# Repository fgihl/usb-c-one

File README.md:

# HIL USB-C Control

A bench device that sits between a Raspberry Pi and a USB-C device under test (DUT). Host software gets controlled access to the DUT's USB 2.0 data, USB-C CC attachment and 5 V VBUS, so it can emulate unplugging and reconnecting the DUT without touching its cable.

It is intended for controlled hardware-in-the-loop (HIL) lab rigs. It is not a general-purpose USB-C charger, dock or power-distribution product.

## Features

- USB 2.0 high-speed hub with a fixed on-board control interface. The Pi always sees the controller, whether or not a DUT is connected.
- Software-controlled J3 (DUT) state: data, CC/Rp and 5 V VBUS are switched independently.
- Priority power mux: external 5 V on J2 is preferred; J1 (the Pi) is the fallback and is reverse-blocked when J2 is valid.
- J3 VBUS is protected by an eFuse (about 3.6 A typical, below 4.0 A worst case) with over-voltage protection, fault reporting and active discharge.
- Fixed 3 A Rp advertisement on J3. No USB PD, BC1.2, VCONN, SuperSpeed or alternate modes.
- One opto-buffered external control line (J4) and test points for the key rails and signals.
- Controlled via `libgpiod` on the standard Linux `cp210x` gpiochip.

## Connectors

| Ref | Role |
|---|---|
| J1 | USB-C upstream to the Raspberry Pi: USB 2.0 data, and fallback VBUS |
| J2 | USB-C 5 V power input (power only, no data). Preferred over J1 |
| J3 | USB-C downstream to the DUT: switched data, CC and VBUS |
| J4 | External opto-buffered control line |

## Architecture

```mermaid
flowchart LR
  J1[J1 USB-C to Pi] -->|D+/D-| H[CH334F USB 2.0 hub]
  J1 -->|VBUS_UP| MUX[TPS2121 priority mux]
  J2[J2 5 V input] -->|VBUS_PWR| MUX
  MUX --> VSYS((VSYS))
  VSYS --> LDO[TLV76733 3.3 V LDO]
  LDO --> H
  H -->|port 1, fixed| C[CP2102N GPIO control]
  H -->|port 2| SW[TS3USB221A data switch]
  SW --> J3[J3 USB-C to DUT]
  LDO --> RP[Rp buffer] --> J3
  VSYS --> EF[TPS259470L eFuse] -->|VBUS_HIL| J3
  C --> EF
  C --> SW
  C --> RP
```

| Function | Part |
|---|---|
| USB 2.0 hub | CH334F |
| Control IC | CP2102N-A02 (7 GPIO) |
| Power mux | TPS2121 |
| J3 eFuse | TPS259470L |
| Data switch | TS3USB221A |
| 3.3 V LDO | TLV76733 |
| Rp buffer | SN74LVC1G125 |
| ESD | TPD4E05U06 |

Board: 4 layers, 50 x 40 mm, top-side SMT, designed for JLCPCB assembly.

## Operating cases

| Case | Power source | Use |
|---|---|---|
| A. Pi-powered | J1 only | Low-current DUTs only. Enumeration, data path and low-power control. |
| B. External 5 V | J2, with the Pi supplying data on J1 | Normal mode for high-current tests. The source must supply the DUT load plus about 0.1 A board consumption (at least 3.5 A for a 3 A DUT). |
| C. Split-cable | External 5 V on J1 VBUS, Pi supplies data and GND | Qualified fixtures only. The Pi-side VBUS must be isolated from the external supply. |

J1 and J2 accept regulated 5 V only. Sustained 12 V or 20 V input is outside the product contract.

## Software contract

Software owns the state machine. The hardware does not detect DUT attach and does not enforce source capability.

- **Disconnect:** data off, wait 20 ms, CC off, wait 20 ms, VBUS off, then wait for the discharge confirmation.
- **Connect:** CC on, VBUS on, confirm VBUS present and no fault, wait 40 ms, data on.

Before a high-current test, confirm that J2 is powering the board. Turn J3 VBUS off before planned J2 removal. The CP2102N GPIO map, configuration image and a control-service example are in [architecture/architecture_final.md](architecture/architecture_final.md) section 6.

## Repository layout

| Path | Contents |
|---|---|
| [product_description.md](product_description.md) | Product requirements, operating cases, accepted limitations, acceptance checks |
| [architecture/architecture_final.md](architecture/architecture_final.md) | Schematic-level architecture, power budget, GPIO map, BOM, risks, prototype tests |
| [architecture/schematic_overview.md](architecture/schematic_overview.md) | Schematic overview |
| [architecture/pcb_floor_plan.md](architecture/pcb_floor_plan.md) | PCB floor plan and layout constraints |
| [llm-kicad/](llm-kicad/) | KiCad 10 project (hierarchical schematic, PCB, custom symbols) |
| [llm-kicad/schematic_review_report.md](llm-kicad/schematic_review_report.md) | Schematic review report and finding log |
| [tools/](tools/) | Audit and helper scripts |

The schematic sheets are `01_power_cc`, `02_usb_hub_control`, `03_dut_interface` and `04_test_validation`. Open `llm-kicad/llm-kicad.kicad_pro` in KiCad 10.

## Tools

`tools/audit_schematic.py` checks symbol pin numbers against placed footprint pad numbers, schematic versus PCB footprint sync, `Value` text versus the JLCPCB catalogue part, and `Datasheet` coverage. It exits non-zero if the pin/pad or footprint-sync checks fail.

```sh
python3 tools/audit_schematic.py
```

### Control scripts

Two self-contained host tools drive the same signal map; neither imports the other.

| Script | Host | Path to the pins |
|---|---|---|
| [code/usb-ctr-mac.py](code/usb-ctr-mac.py) | macOS | CP2102N vendor requests over libusb (pyusb) |
| [code/usb-ctr-linux.py](code/usb-ctr-linux.py) | Linux | kernel `cp210x` gpiochip (uAPI v2); usbfs for NVM reads |

Both auto-detect the board generation from the CP2102N part number and, on a QFN24, the NVM Release Version:

| Board | Part | Lines | Release Version |
|---|---|---|---|
| V2.0 | CP2102N QFN28 | 7 | `0x0200` (2.00) |
| usb-passthrough v1.1 | CP2102N QFN24 | 4 | `0x0101` (1.01, CC_EN inverted) |
| usb-passthrough v1.0 | CP2102N QFN24 | 4 | `0x0100` (1.00) |

`--board auto|v2.0|v1.1|v1.0` overrides the detection. `info` reports the identity and the programmed image, `check` is the NVM read-back gate and `verify` the full per-unit acceptance check; both accept `--record code/fleet-record.tsv`. The legacy boards have no VBUS sense, source select or opto line, so `on`/`off` substitute a settle delay for the VBUS confirmation, `ext` is refused and `--high-current` cannot be checked.

## Known limitations

- Fixed 3 A Rp: the advertisement can exceed the active source's real capacity.
- No hardware DUT-attach detection: an unplugged DUT can leave J3 VBUS live until software disables it.
- A single priority mux is the only isolation between J1 and J2. It is not an independent-source isolator, and a split cable that joins an external supply to the Pi is not protected against.
- No per-input current limit or input over-voltage disconnect.

The full list and the release acceptance checks are in [product_description.md](product_description.md) sections 7 to 9.

## Status

Hardware revision V2.0. **Five units are built, identified 1-5**, each programmed
with the CP2102N configuration image carrying **Release Version 2.00**
(`0x0200`) — the host reads this back as `bcdDevice` = `0x0200`, though only
after the board has been power-cycled. **All five units were verified
2026-10-14**: correct configuration image and power-up safe state, VBUS rising in
18–21 ms, and a USB mass-storage DUT enumerating at J3 on connect and dropping
off on disconnect. Per-unit evidence is in `code/fleet-record.tsv`. The unit ID is carried in the CP2102N USB
serial descriptor (`0001`-`0005`); the manufacturer and product strings stay at
the Silicon Labs defaults, so the serial descriptor is what distinguishes one
unit from another. See
[architecture/architecture_final.md](architecture/architecture_final.md)
section 6.3 for the Release Version and serial-number policies and the per-unit
read-back gate.

The legacy **usb-passthrough v1.1** units now carry a programmed CP2102N image
too: Release Version **1.01** (`0x0101`, which names the inverted-CC v1.1 pin
map) plus a fleet serial in the serial descriptor (`0006`, `0010`, …). Their
GPIO bytes stay at the factory open-drain/latched-high settings, so the existing
board wiring is unchanged. `check` reports PASS for such a unit and records the
read-back in `code/fleet-record.tsv` with `board = v1.1`; the host only sees the
new serial and `bcdDevice` after a power-on reset, so replug the board after
programming.

Before release, see the open items in the schematic review report and the mandatory prototype tests in [architecture/architecture_final.md](architecture/architecture_final.md) section 10. The CP2102N must be programmed with the configuration image before use.

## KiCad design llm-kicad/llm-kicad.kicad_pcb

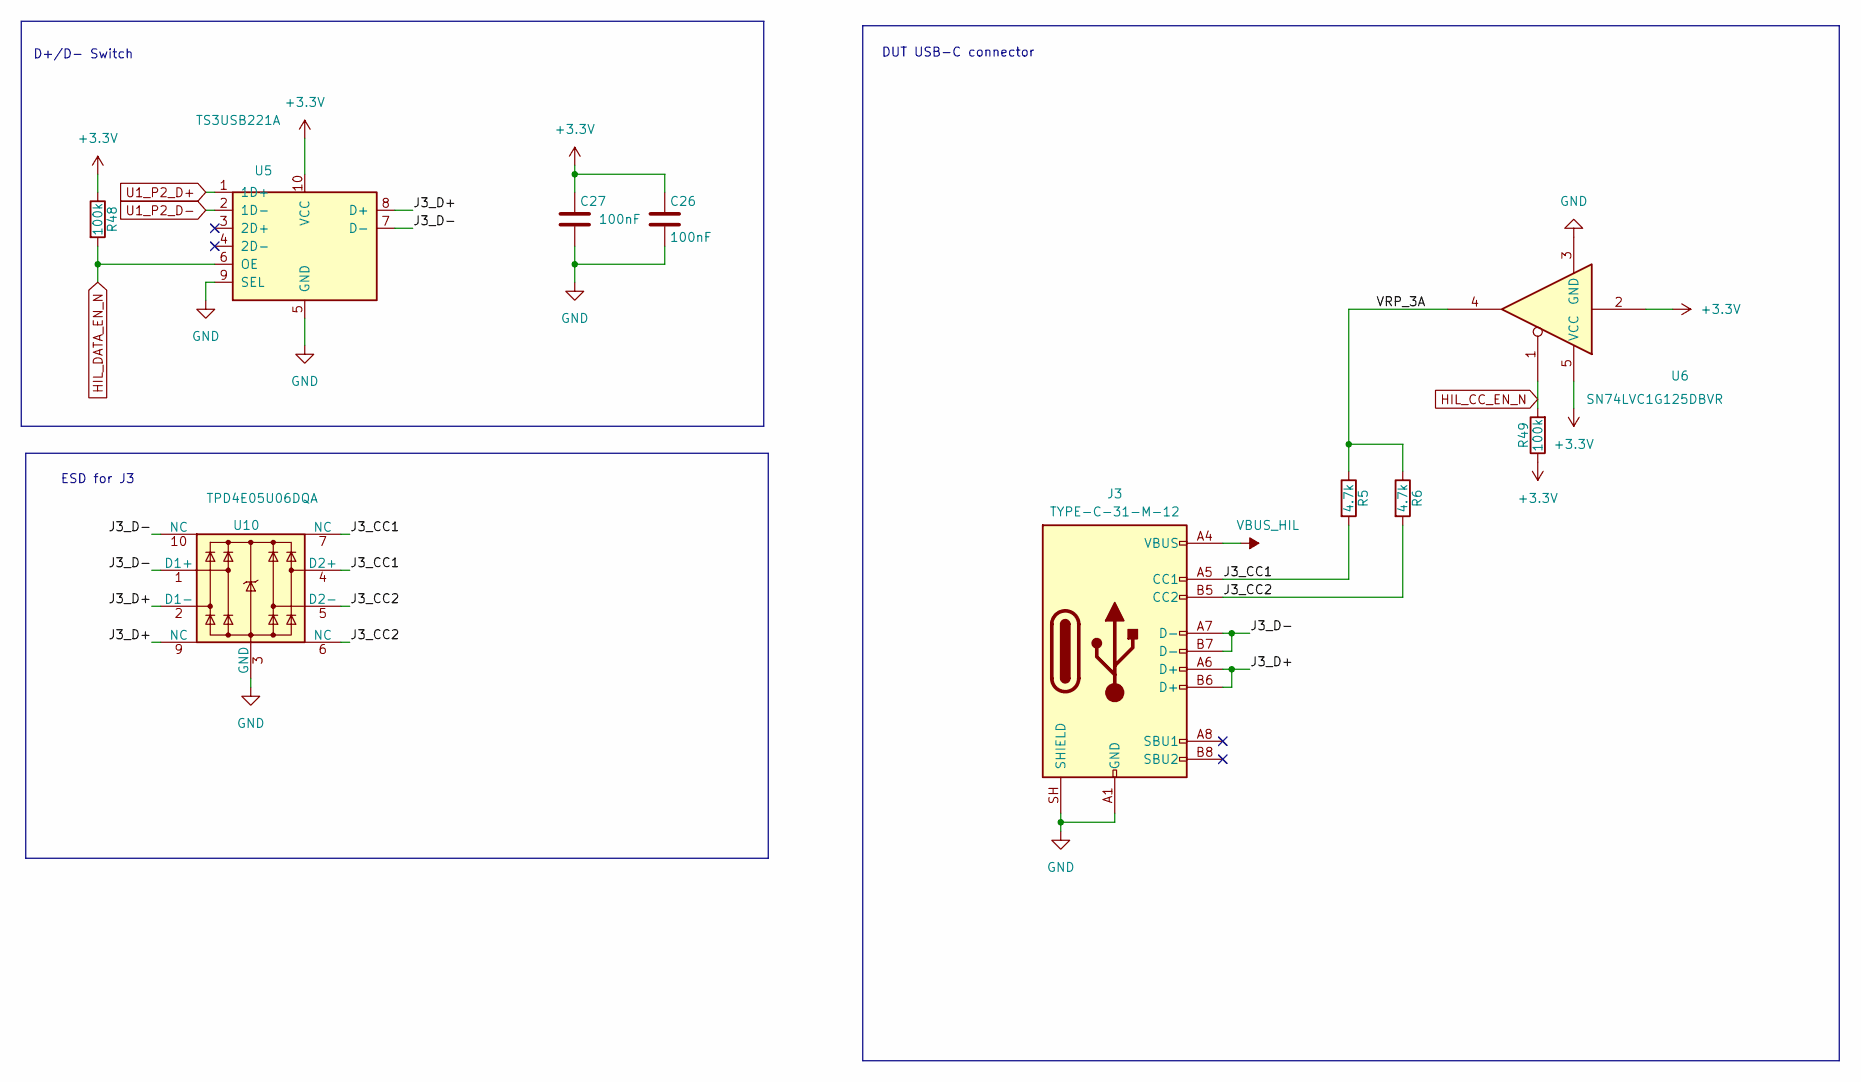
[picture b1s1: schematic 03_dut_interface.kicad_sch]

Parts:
C26, C27: 100nF; C_0402_1005Metric; LCSC C1525
J3: TYPE-C-31-M-12; USB_C_Receptacle_HRO_TYPE-C-31-M-12; LCSC C165948
R5, R6: 4.7k; R_0402_1005Metric; LCSC C25900
R48, R49: 100k; R_0402_1005Metric; LCSC C25741
U5: TS3USB221A; Texas_UQFN-10_1.5x2mm_P0.5mm; LCSC C128396
U6: SN74LVC1G125DBVR; SOT-23-5; LCSC C23654
U10: TPD4E05U06DQA; USON-10_2.5x1.0mm_P0.5mm; LCSC C138714

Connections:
+3.3V: C26.1, C27.1, R48.1, R49.1, U5.10 (VCC), U6.2, U6.5 (VCC); also elsewhere on the board
/DUT Interface/J3_CC1: J3.A5 (CC1), R5.2, U10.4 (D2+), U10.7 (NC)
/DUT Interface/J3_CC2: J3.B5 (CC2), R6.2, U10.5 (D2-), U10.6 (NC)
/DUT Interface/J3_D+: J3.A6 (D+), J3.B6 (D+), U5.8 (D+), U10.2 (D1-), U10.9 (NC)
/DUT Interface/J3_D-: J3.A7 (D-), J3.B7 (D-), U5.7 (D-), U10.1 (D1+), U10.10 (NC)
/DUT Interface/VRP_3A: R5.1, R6.1, U6.4
GND: C26.2, C27.2, J3.A1 (GND), J3.A12 (GND), J3.B1 (GND), J3.B12 (GND), J3.SH (SHIELD), U5.5 (GND), U5.9 (SEL), U6.3 (GND), U10.3 (GND), U10.8 (GND); also elsewhere on the board
HIL_CC_EN_N: R49.2, U6.1; also elsewhere on the board
HIL_DATA_EN_N: R48.2, U5.6 (OE); also elsewhere on the board
U1_P2_D+: U5.1 (1D+); also elsewhere on the board
U1_P2_D-: U5.2 (1D-); also elsewhere on the board
VBUS_HIL: J3.A4 (VBUS), J3.A9 (VBUS), J3.B4 (VBUS), J3.B9 (VBUS); also elsewhere on the board

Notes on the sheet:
DUT USB-C connector
ESD for J3
D+/D- Switch

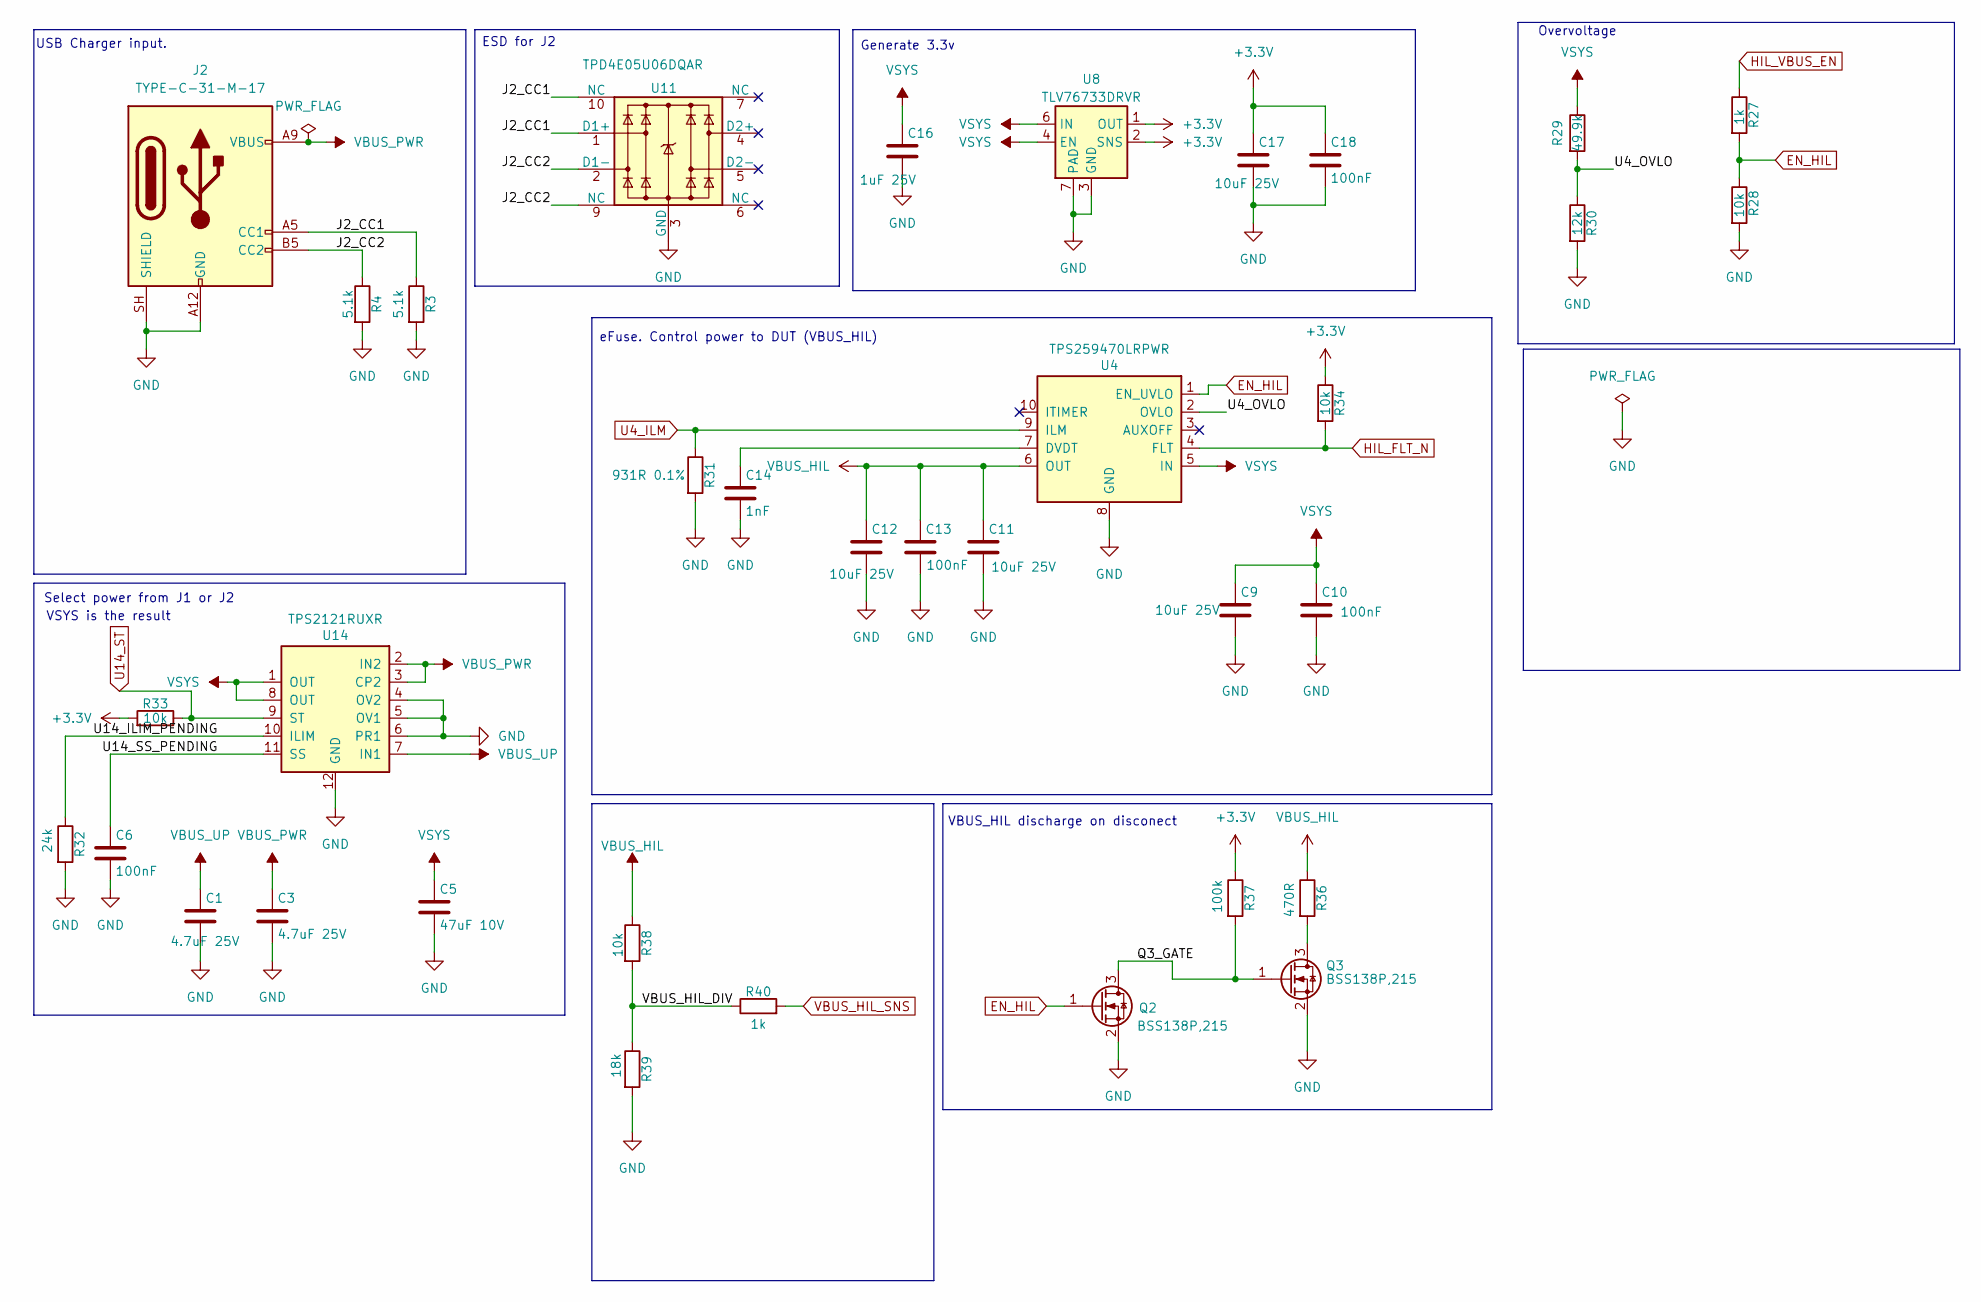
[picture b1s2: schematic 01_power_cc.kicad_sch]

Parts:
C1, C3: 4.7uF 25V; C_0805_2012Metric; LCSC C1779
C5: 47uF 10V; C_1206_3216Metric; LCSC C96123
C6, C10, C13, C18: 100nF; C_0402_1005Metric; LCSC C1525
C9, C11, C12, C17: 10uF 25V; C_0805_2012Metric; LCSC C15850
C14: 1nF; C_0402_1005Metric; LCSC C1523
C16: 1uF 25V; C_0402_1005Metric; LCSC C52923
J2: TYPE-C-31-M-17; USB_C_Receptacle_HRO_TYPE-C-31-M-17; LCSC C283540
Q2, Q3: BSS138P,215; SOT-23; LCSC C75547
R3, R4: 5.1k; R_0402_1005Metric; LCSC C25905
R27, R40: 1k; R_0402_1005Metric; LCSC C11702
R28, R33, R34, R38: 10k; R_0402_1005Metric; LCSC C25744
R29: 49.9k; R_0402_1005Metric; LCSC C25897
R30: 12k; R_0402_1005Metric; LCSC C25752
R31: 931R 0.1%; R_0402_1005Metric; LCSC C852955
R32: 24k; R_0402_1005Metric; LCSC C25769
R36: 470R; R_0805_2012Metric; LCSC C17710
R37: 100k; R_0402_1005Metric; LCSC C25741
R39: 18k; R_0402_1005Metric; LCSC C25762
U4: TPS259470LRPWR; LCSC C3662793
U8: TLV76733DRVR; WSON-6-1EP_2x2mm_P0.65mm_EP1x1.6mm_ThermalVias; LCSC C2848334
U11: TPD4E05U06DQAR; USON-10_2.5x1.0mm_P0.5mm; LCSC C138714
U14: TPS2121RUXR; Texas_VQFN-HR-12_2x2.5mm_P0.5mm; LCSC C485916

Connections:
+3.3V: C17.1, C18.1, R33.2, R34.1, R37.1, U8.1 (OUT), U8.2 (SNS); also elsewhere on the board
/Power and CC/J2_CC1: J2.A5 (CC1), R3.1, U11.1 (D1+), U11.10 (NC)
/Power and CC/J2_CC2: J2.B5 (CC2), R4.1, U11.2 (D1-), U11.9 (NC)
/Power and CC/Q3_GATE: Q2.3 (D), Q3.1 (G), R37.2
/Power and CC/U4_OVLO: R29.2, R30.1, U4.2 (OVLO)
/Power and CC/U14_ILIM_PENDING: R32.1, U14.10 (ILIM)
/Power and CC/U14_SS_PENDING: C6.1, U14.11 (SS)
/Power and CC/VBUS_HIL_DIV: R38.2, R39.1, R40.1
EN_HIL: Q2.1 (G), R27.2, R28.1, U4.1 (EN_UVLO); also elsewhere on the board
GND: C1.2, C3.2, C5.2, C6.2, C9.2, C10.2, C11.2, C12.2, C13.2, C14.2, C16.2, C17.2, C18.2, J2.A12 (GND), J2.B12 (GND), J2.SH (SHIELD), Q2.2 (S), Q3.2 (S), R3.2, R4.2, R28.2, R30.2, R31.2, R32.2, R39.2, U4.8 (GND), U8.3 (GND), U8.5 (GND), U8.7 (PAD), U11.3 (GND), U11.8 (GND), U14.4 (OV2), U14.5 (OV1), U14.6 (PR1), U14.12 (GND); also elsewhere on the board
HIL_FLT_N: R34.2, U4.4 (FLT); also elsewhere on the board
HIL_VBUS_EN: R27.1; also elsewhere on the board
unnamed: Q3.3 (D), R36.2
unnamed: C14.1, U4.7 (DVDT)
U4_ILM: R31.1, U4.9 (ILM); also elsewhere on the board
U14_ST: R33.1, U14.9 (ST); also elsewhere on the board
VBUS_HIL: C11.1, C12.1, C13.1, R36.1, R38.1, U4.6 (OUT); also elsewhere on the board
VBUS_HIL_SNS: R40.2; also elsewhere on the board
VBUS_PWR: C3.1, J2.A9 (VBUS), J2.B9 (VBUS), U14.2 (IN2), U14.3 (CP2); also elsewhere on the board
VBUS_UP: C1.1, U14.7 (IN1); also elsewhere on the board
VSYS: C5.1, C9.1, C10.1, C16.1, R29.1, U4.5 (IN), U8.4 (EN), U8.6 (IN), U14.1 (OUT), U14.8 (OUT); also elsewhere on the board

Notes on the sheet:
Generate 3.3v
USB Charger input.
Overvoltage
ESD for J2
VSYS is the result
VBUS_HIL discharge on disconect
Select power from J1 or J2
eFuse. Control power to DUT (VBUS_HIL)

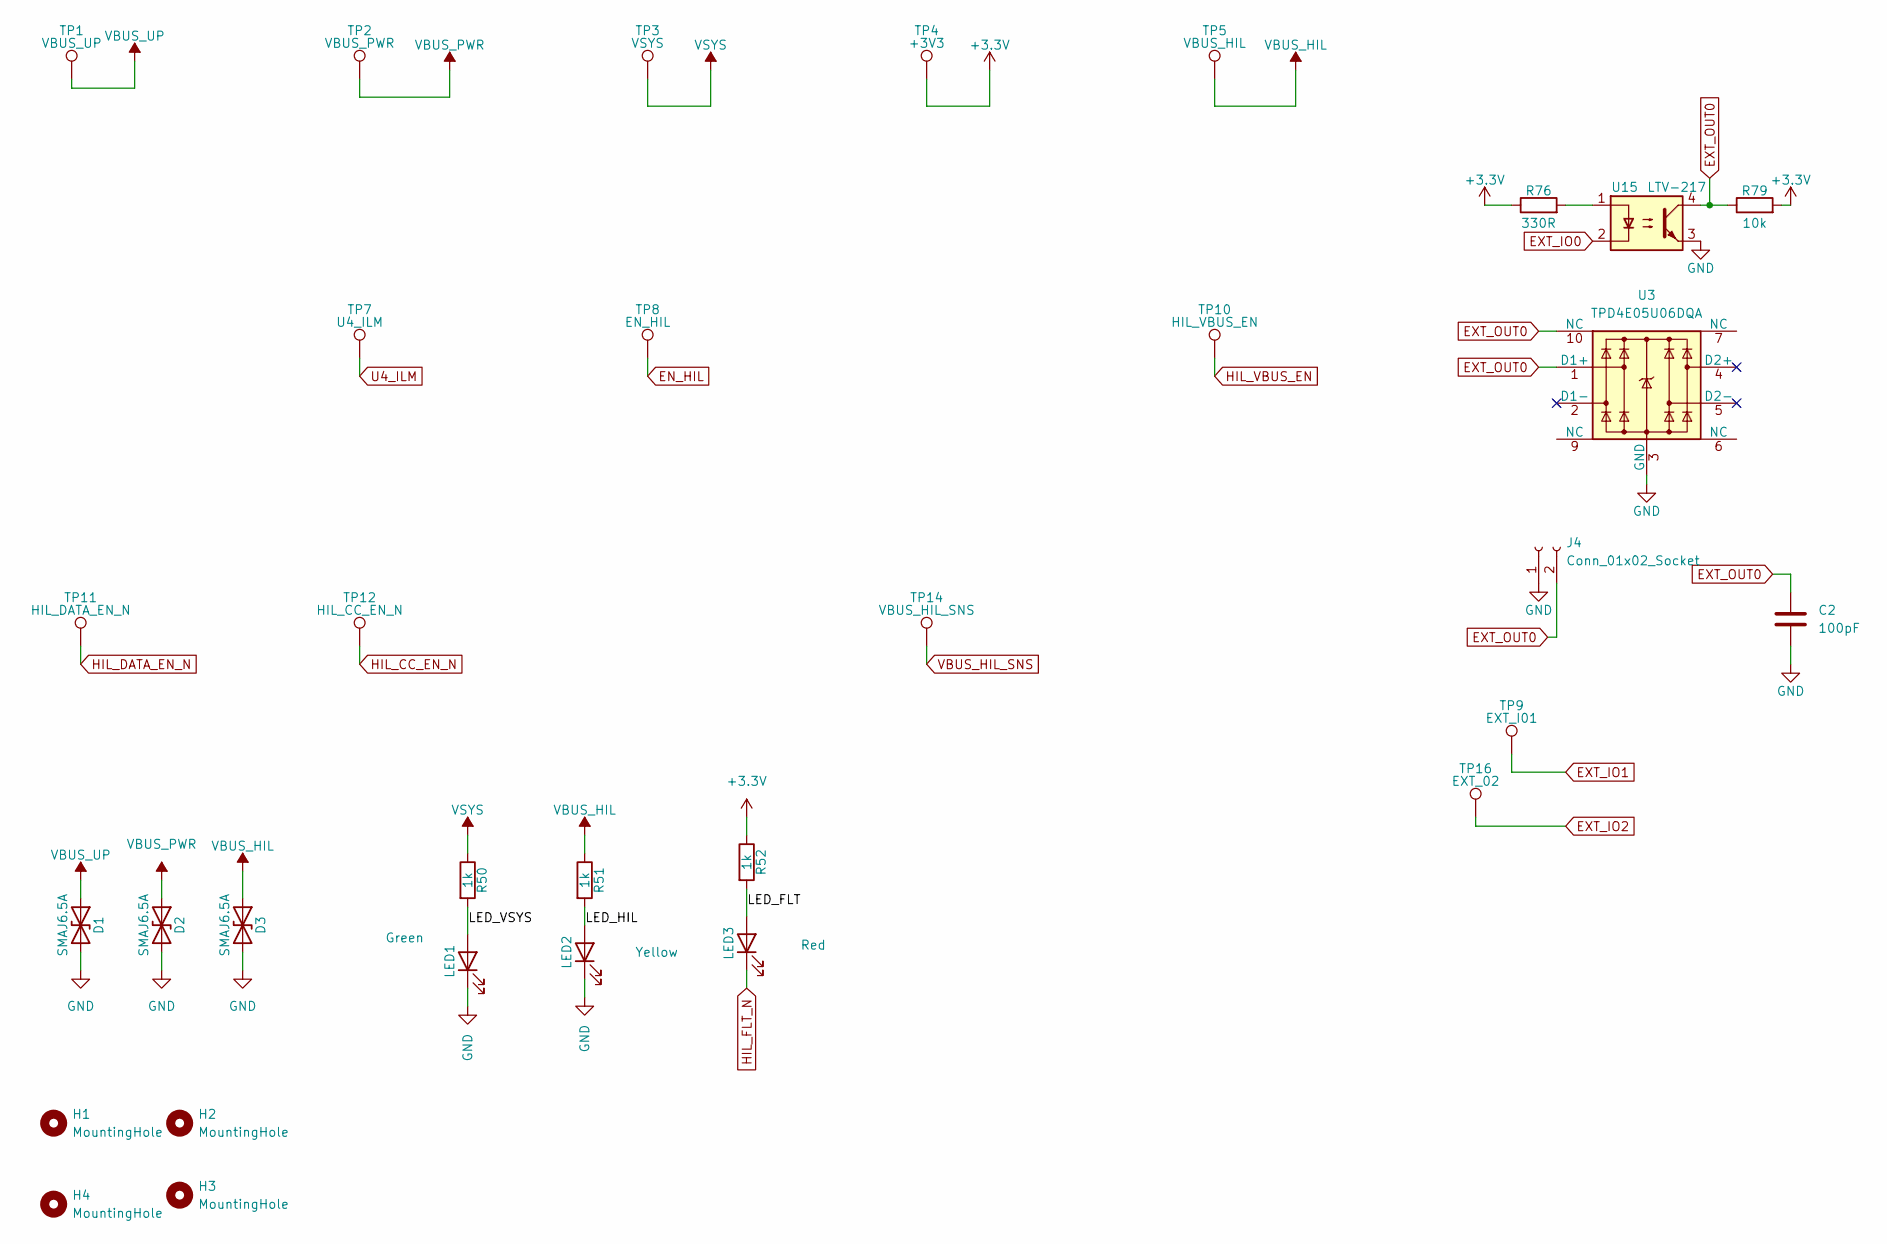
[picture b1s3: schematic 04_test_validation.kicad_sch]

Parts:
C2: 100pF; C_0402_1005Metric; LCSC C1546
D1, D2, D3: SMAJ6.5A; D_SMA; LCSC C123817
H1, H2, H3, H4: MountingHole; MountingHole_2.2mm_M2
J4: Conn_01x02_Socket; PinHeader_1x02_P2.54mm_Vertical
LED1: Green; LED_0805_2012Metric; LCSC C2297
LED2: Yellow; LED_0805_2012Metric; LCSC C2296
LED3: Red; LED_0603_1608Metric; LCSC C2286
R50, R51, R52: 1k; R_0402_1005Metric; LCSC C11702
R76: 330R; R_0402_1005Metric; LCSC C25104
R79: 10k; R_0402_1005Metric; LCSC C25744
TP1: VBUS_UP; TestPoint_Pad_D1.5mm
TP2: VBUS_PWR; TestPoint_Pad_D1.5mm
TP3: VSYS; TestPoint_Pad_D1.5mm
TP4: +3V3; TestPoint_Pad_D1.5mm
TP5: VBUS_HIL; TestPoint_Pad_D2.0mm
TP7: U4_ILM; TestPoint_Pad_D1.5mm
TP8: EN_HIL; TestPoint_Pad_D1.5mm
TP9: EXT_I01; TestPoint_Pad_D1.5mm
TP10: HIL_VBUS_EN; TestPoint_Pad_D1.5mm
TP11: HIL_DATA_EN_N; TestPoint_Pad_D1.5mm
TP12: HIL_CC_EN_N; TestPoint_Pad_D1.5mm
TP14: VBUS_HIL_SNS; TestPoint_Pad_D1.5mm
TP16: EXT_02; TestPoint_Pad_D1.5mm
U3: TPD4E05U06DQA; USON-10_2.5x1.0mm_P0.5mm; LCSC C138714
U15: LTV-217; SOP-4_4.4x2.6mm_P1.27mm; LCSC C115450

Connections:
+3.3V: R52.1, R76.1, R79.2, TP4.1 (1_1); also elsewhere on the board
/Test and Validation/LED_FLT: LED3.2 (A), R52.2
/Test and Validation/LED_HIL: LED2.2 (A), R51.2
/Test and Validation/LED_VSYS: LED1.2 (A), R50.2
EN_HIL: TP8.1 (1_1); also elsewhere on the board
EXT_IO0: U15.2; also elsewhere on the board
EXT_IO1: TP9.1 (1_1); also elsewhere on the board
EXT_IO2: TP16.1 (1_1); also elsewhere on the board
EXT_OUT0: C2.1, J4.2, R79.1, U3.1 (D1+), U3.10 (NC), U15.4
GND: C2.2, D1.2 (A2), D2.2 (A2), D3.2 (A2), J4.1, LED1.1 (K), LED2.1 (K), U3.3 (GND), U3.8 (GND), U15.3; also elsewhere on the board
HIL_CC_EN_N: TP12.1 (1_1); also elsewhere on the board
HIL_DATA_EN_N: TP11.1 (1_1); also elsewhere on the board
HIL_FLT_N: LED3.1 (K); also elsewhere on the board
HIL_VBUS_EN: TP10.1 (1_1); also elsewhere on the board
unnamed: R76.2, U15.1
U4_ILM: TP7.1 (1_1); also elsewhere on the board
VBUS_HIL: D3.1 (A1), R51.1, TP5.1 (1_1); also elsewhere on the board
VBUS_HIL_SNS: TP14.1 (1_1); also elsewhere on the board
VBUS_PWR: D2.1 (A1), TP2.1 (1_1); also elsewhere on the board
VBUS_UP: D1.1 (A1), TP1.1 (1_1); also elsewhere on the board
VSYS: R50.1, TP3.1 (1_1); also elsewhere on the board

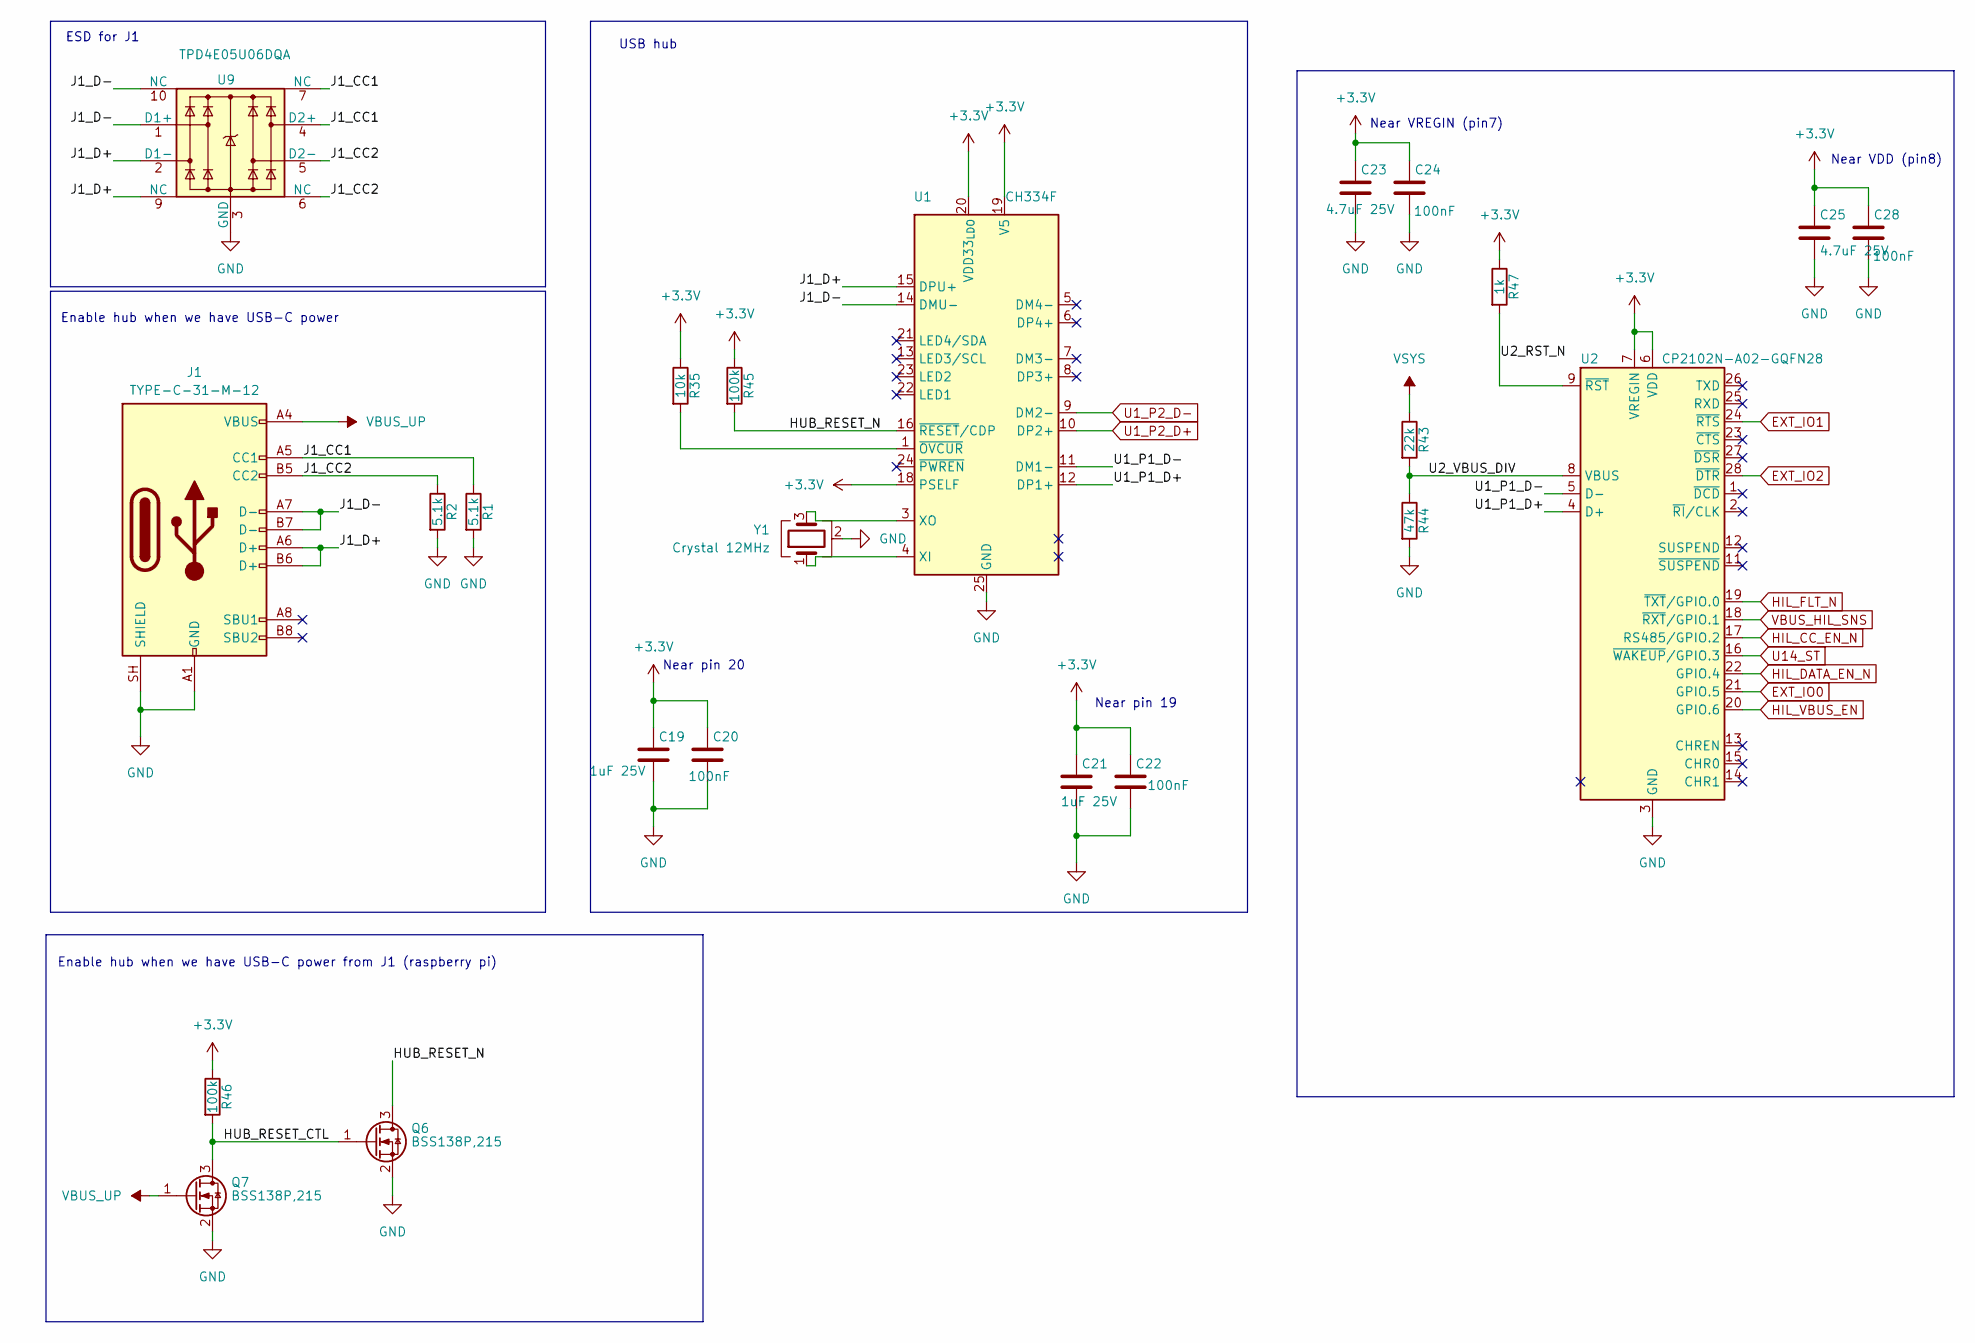
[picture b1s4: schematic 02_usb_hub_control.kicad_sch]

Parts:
C19, C21: 1uF 25V; C_0402_1005Metric; LCSC C52923
C20, C22, C24, C28: 100nF; C_0402_1005Metric; LCSC C1525
C23, C25: 4.7uF 25V; C_0805_2012Metric; LCSC C1779
J1: TYPE-C-31-M-12; USB_C_Receptacle_HRO_TYPE-C-31-M-12; LCSC C165948
Q6, Q7: BSS138P,215; SOT-23; LCSC C75547
R1, R2: 5.1k; R_0402_1005Metric; LCSC C25905
R35: 10k; R_0402_1005Metric; LCSC C25744
R43: 22k; R_0402_1005Metric; LCSC C25768
R44: 47k; R_0402_1005Metric; LCSC C25792
R45, R46: 100k; R_0402_1005Metric; LCSC C25741
R47: 1k; R_0402_1005Metric; LCSC C11702
U1: CH334F; QFN-24-1EP_4x4mm_P0.5mm_EP2.7x2.7mm; LCSC C5187527
U2: CP2102N-A02-GQFN28; QFN-28-1EP_5x5mm_P0.5mm_EP3.25x3.25mm; LCSC C964632
U9: TPD4E05U06DQA; USON-10_2.5x1.0mm_P0.5mm; LCSC C138714
Y1: Crystal 12MHz; Crystal_SMD_3225-4Pin_3.2x2.5mm; LCSC C9002

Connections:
+3.3V: C19.1, C20.1, C21.1, C22.1, C23.1, C24.1, C25.1, C28.1, R35.1, R45.1, R46.1, R47.1, U1.18 (PSELF), U1.19 (V5), U1.20 (VDD33_{LDO}), U2.6 (VDD), U2.7 (VREGIN); also elsewhere on the board
/USB Hub and Control/HUB_RESET_CTL: Q6.1 (G), Q7.3 (D), R46.2
/USB Hub and Control/HUB_RESET_N: Q6.3 (D), R45.2, U1.16 (~RESET/CDP)
/USB Hub and Control/J1_CC1: J1.A5 (CC1), R1.1, U9.4 (D2+), U9.7 (NC)
/USB Hub and Control/J1_CC2: J1.B5 (CC2), R2.1, U9.5 (D2-), U9.6 (NC)
/USB Hub and Control/J1_D+: J1.A6 (D+), J1.B6 (D+), U1.15 (DPU+), U9.2 (D1-), U9.9 (NC)
/USB Hub and Control/J1_D-: J1.A7 (D-), J1.B7 (D-), U1.14 (DMU-), U9.1 (D1+), U9.10 (NC)
/USB Hub and Control/U1_P1_D+: U1.12 (DP1+), U2.4 (D+)
/USB Hub and Control/U1_P1_D-: U1.11 (DM1-), U2.5 (D-)
/USB Hub and Control/U2_RST_N: R47.2, U2.9 (~RST)
/USB Hub and Control/U2_VBUS_DIV: R43.2, R44.1, U2.8 (VBUS)
EXT_IO0: U2.21 (GPIO.5); also elsewhere on the board
EXT_IO1: U2.24 (~RTS); also elsewhere on the board
EXT_IO2: U2.28 (~DTR); also elsewhere on the board
GND: C19.2, C20.2, C21.2, C22.2, C23.2, C24.2, C25.2, C28.2, J1.A1 (GND), J1.A12 (GND), J1.B1 (GND), J1.B12 (GND), J1.SH (SHIELD), Q6.2 (S), Q7.2 (S), R1.2, R2.2, R44.2, U1.25 (GND), U2.3 (GND), U2.29 (GND), U9.3 (GND), U9.8 (GND), Y1.2 (G), Y1.4 (G); also elsewhere on the board
HIL_CC_EN_N: U2.17 (RS485/GPIO.2); also elsewhere on the board
HIL_DATA_EN_N: U2.22 (GPIO.4); also elsewhere on the board
HIL_FLT_N: U2.19 (~TXT/GPIO.0); also elsewhere on the board
HIL_VBUS_EN: U2.20 (GPIO.6); also elsewhere on the board
unnamed: U1.4 (XI), Y1.1
unnamed: U1.3 (XO), Y1.3
unnamed: R35.2, U1.1 (~OVCUR)
U1_P2_D+: U1.10 (DP2+); also elsewhere on the board
U1_P2_D-: U1.9 (DM2-); also elsewhere on the board
U14_ST: U2.16 (~WAKEUP/GPIO.3); also elsewhere on the board
VBUS_HIL_SNS: U2.18 (~RXT/GPIO.1); also elsewhere on the board
VBUS_UP: J1.A4 (VBUS), J1.A9 (VBUS), J1.B4 (VBUS), J1.B9 (VBUS), Q7.1 (G); also elsewhere on the board
VSYS: R43.1; also elsewhere on the board

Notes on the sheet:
Near VDD (pin8)
Enable hub when we have USB-C power
ESD for J1
Near VREGIN (pin7)
USB hub
Near pin 20
Enable hub when we have USB-C power from J1 (raspberry pi)
Near pin 19

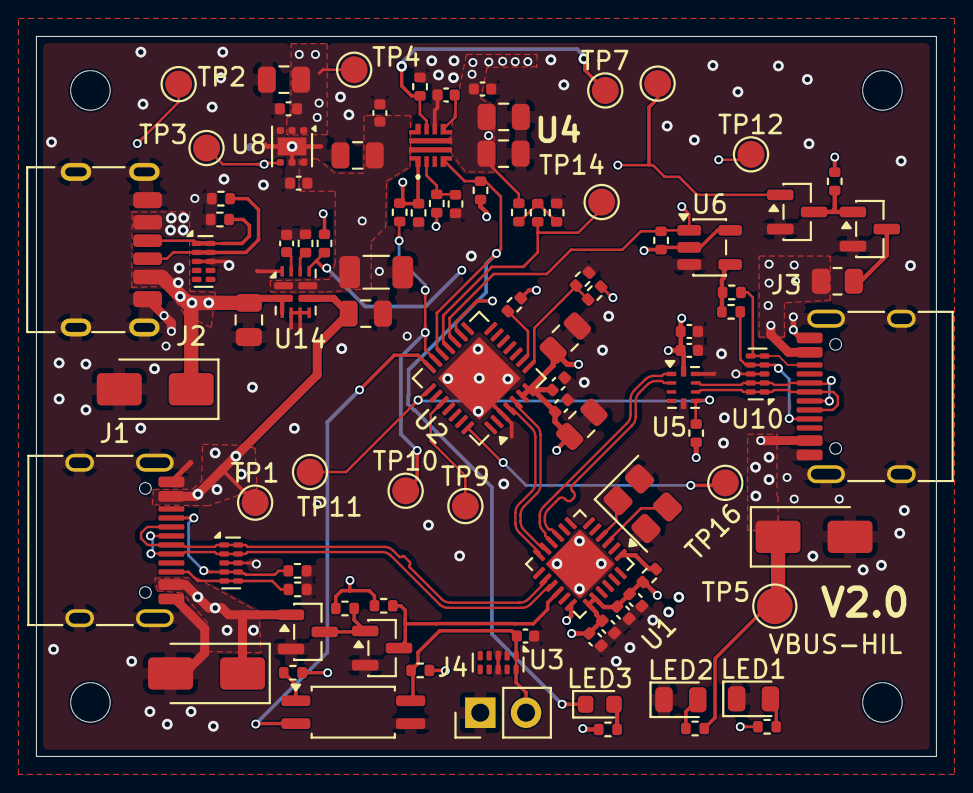
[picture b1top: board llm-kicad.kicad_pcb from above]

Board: 4 copper layers, 50.0 x 40.0 mm, 100 parts (0 on the bottom side), 51 nets.

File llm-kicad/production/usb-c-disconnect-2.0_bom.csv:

Designator,Footprint,Quantity,Value,LCSC Part #
"C1, C23, C25, C3",0805,4,4.7uF 25V,C1779
"C10, C13, C20, C22, C24, C26, C27, C28, C6",0402,9,100nF,C1525
"C11, C12, C9",0805,3,10uF 25V,C15850
C14,0402,1,1nF,C1523
C16,0402,1,1uF 0402 25V,C52923
C17,0805,1,10uF 0805 25V,C15850
C18,0402,1,100nF 0402,C1525
"C19, C21",0402,2,1uF 25V,C52923
C2,0402,1,100pF,C1546
C5,1206,1,47uF 10V,C96123
"D1, D2, D3",D_SMA,3,SMAJ6.5A,C123817
"H1, H2, H3, H4",MountingHole_2.2mm_M2,4,MountingHole,
"J1, J3",USB_C_Receptacle_HRO_TYPE-C-31-M-12,2,TYPE-C-31-M-12,C165948
J2,USB_C_Receptacle_HRO_TYPE-C-31-M-17,1,TYPE-C-31-M-17,C283540
J4,PinHeader_1x02_P2.54mm_Vertical,1,Conn_01x02_Socket,
LED1,0805,1,Green,C2297
LED2,0805,1,Yellow,C2296
LED3,0603,1,Red,C2286
"Q2, Q3, Q6, Q7",SOT-23,4,"BSS138P,215",C75547
"R1, R2",0402,2,5.1k,C25905
"R27, R47, R50, R51, R52",0402,5,1k,C11702
"R28, R33, R34, R35",0402,4,10k,C25744
R29,0402,1,49.9k,C25897
"R3, R4",0402,2,5.1k 0402,C25905
R30,0402,1,12k,C25752
R31,0402,1,931R 0.1%,C852955
R32,0402,1,24k,C25769
R36,0805,1,470R 0805,C17710
R37,0402,1,100k 0402,C25741
"R38, R79",0402,2,10k 0402,C25744
R39,0402,1,18k 0402,C25762
R40,0402,1,1k 0402,C11702
R43,0402,1,22k,C25768
R44,0402,1,47k,C25792
"R45, R46, R48, R49",0402,4,100k,C25741
"R5, R6",0402,2,4.7k,C25900
R76,0402,1,330R 0402,C25104
TP1,TestPoint_Pad_D1.5mm,1,VBUS_UP,
TP10,TestPoint_Pad_D1.5mm,1,HIL_VBUS_EN,
TP11,TestPoint_Pad_D1.5mm,1,HIL_DATA_EN_N,
TP12,TestPoint_Pad_D1.5mm,1,HIL_CC_EN_N,
TP14,TestPoint_Pad_D1.5mm,1,VBUS_HIL_SNS,
TP16,TestPoint_Pad_D1.5mm,1,EXT_02,
TP2,TestPoint_Pad_D1.5mm,1,VBUS_PWR,
TP3,TestPoint_Pad_D1.5mm,1,VSYS,
TP4,TestPoint_Pad_D1.5mm,1,+3V3,
TP5,TestPoint_Pad_D2.0mm,1,VBUS_HIL,
TP7,TestPoint_Pad_D1.5mm,1,U4_ILM,
TP8,TestPoint_Pad_D1.5mm,1,EN_HIL,
TP9,TestPoint_Pad_D1.5mm,1,EXT_I01,
U1,QFN-24-1EP_4x4mm_P0.5mm_EP2.7x2.7mm,1,CH334F,C5187527
"U10, U3, U9",USON-10_2.5x1.0mm_P0.5mm,3,TPD4E05U06DQA,C138714
U11,USON-10_2.5x1.0mm_P0.5mm,1,TPD4E05U06DQAR,C138714
U14,Texas_VQFN-HR-12_2x2.5mm_P0.5mm,1,TPS2121RUXR,C485916
U15,SOP-4_4.4x2.6mm_P1.27mm,1,LTV-217,C115450
U2,QFN-28-1EP_5x5mm_P0.5mm_EP3.25x3.25mm,1,CP2102N-A02-GQFN28,C964632
U4,TPS259470LRPWR,1,TPS259470LRPWR,C3662793
U5,Texas_UQFN-10_1.5x2mm_P0.5mm,1,TS3USB221A,C128396
U6,SOT-23-5,1,SN74LVC1G125DBVR,C23654
U8,WSON-6-1EP_2x2mm_P0.65mm_EP1x1.6mm_ThermalVias,1,TLV76733DRVR,C2848334
Y1,Crystal_SMD_3225-4Pin_3.2x2.5mm,1,Crystal 12MHz,C9002

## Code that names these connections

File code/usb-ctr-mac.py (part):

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
GPIO_COUNT = 7

HIL_FLT_N = 0    # in,  low  = U4 reports a fault
VBUS_SNS = 1     # in,  high = VBUS_HIL present at J3
CC_EN_N = 2      # out, low  = Rp presented  (open-drain)
U14_ST = 3       # in,  low  = VBUS_PWR (J2) is the active source
DATA_EN_N = 4    # out, low  = data path closed  (open-drain)
EXT_IO0 = 5      # out, low  = opto LED on, J4 line asserted  (open-drain)
VBUS_EN = 6      # out, high = eFuse enabled  (push-pull)

OUTPUT_PINS = (CC_EN_N, DATA_EN_N, EXT_IO0, VBUS_EN)

# Power-up safe state per section 6.1: every output in its "off" position.
SAFE_STATE = {
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        """'vbus_pwr' / 'vbus_up', or None when there is no source select."""
        if self.source_pin is None:
            return None
        return "vbus_up" if self._bit(snap, self.source_pin) else "vbus_pwr"

    def ext_asserted(self, snap):
        """True/False for the J4 opto line, or None when it does not exist."""
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    outputs=OUTPUT_PINS,
    safe_state=SAFE_STATE,
    cc_pin=CC_EN_N, data_pin=DATA_EN_N, vbus_pin=VBUS_EN,
    fault_pin=HIL_FLT_N, sense_pin=VBUS_SNS, source_pin=U14_ST, ext_pin=EXT_IO0,
    cc_connected_level=0, data_connected_level=0, vbus_on_level=1,
    pushpull_pins=(VBUS_EN,),
)
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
